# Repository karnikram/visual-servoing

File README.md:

<h1 align="center">Visual Servoing of Mobile Robot</h1>

This repo contains code for controlling a differential drive mobile robot within a map using images from an overhead camera. Uses thresholding and template matching for localization and a PID controller for generating the steering commands. The mobile robot uses an Arduino as its controller and LibSerial is used for communicating with it.

Also included are the PCB files for the mobile robot controller board.

<div align="center">

</div>

<a href="https://www.youtube.com/watch?v=kU-pIHazJII">Video</a>

### Libraries Used
* [OpenCV](https://github.com/opencv/opencv)
* [LibSerial](http://libserial.sourceforge.net/x27.html)

Based on [LOCK](https://github.com/QuinAsura/LOCK).

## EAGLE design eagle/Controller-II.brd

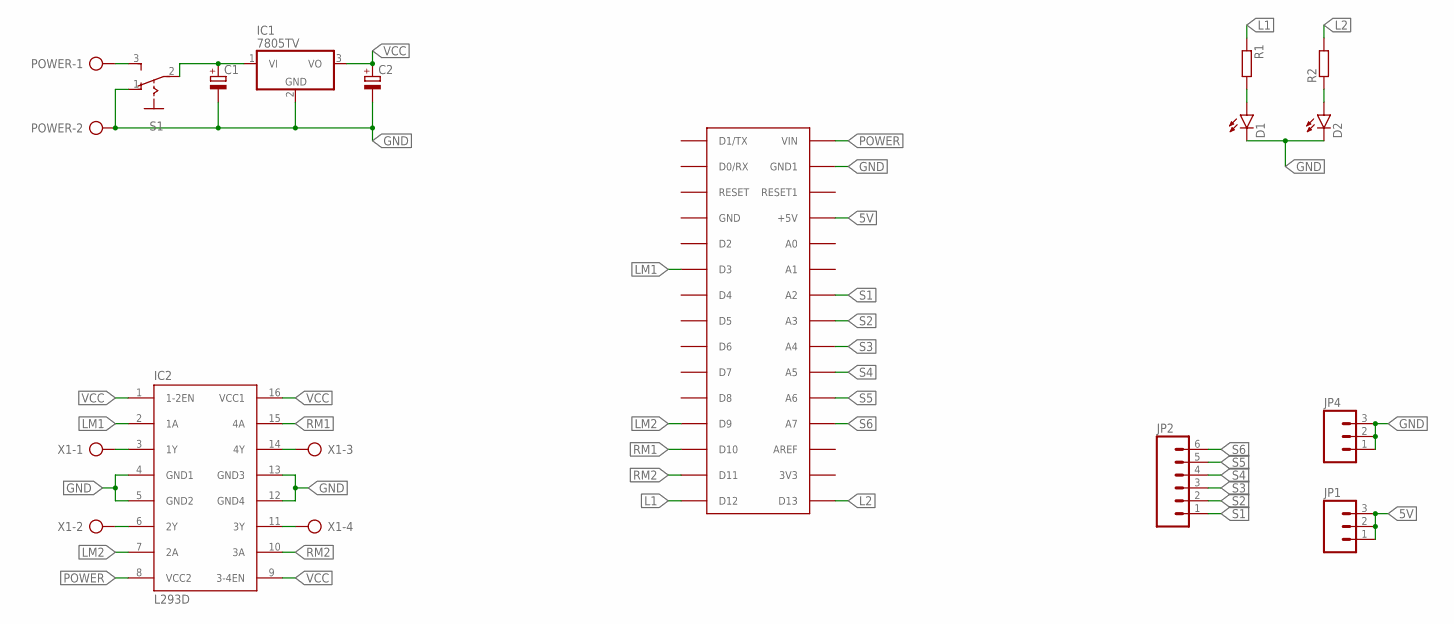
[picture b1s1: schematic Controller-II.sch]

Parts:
C1, C2: CPOL-EUE5-10.5; E5-10,5
D1, D2: LED5MM
IC1: 7805TV; TO220V
IC2: L293D; DIL16
JP1, JP4: M031X03_NO_SILK; 1X03_NO_SILK
JP2: M06NO_SILK_FEMALE_PTH; 1X06_NO_SILK
POWER: AK300/2
R1, R2: R-EU_0204/5; 0204/5
S1: 255SB
U1: ARDUINONANO; PDIP-32
X1: AK300/4

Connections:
5V: JP1.1, JP1.2, JP1.3, U1.+5V
7805: C1.+, IC1.1 (VI), S1.2
GND: C1.-, C2.-, D1.K (C), D2.K (C), IC1.2 (GND), IC2.4 (GND1), IC2.5 (GND2), IC2.12 (GND4), IC2.13 (GND3), JP4.1, JP4.2, JP4.3, POWER.2, S1.1 (O), U1.GND1
L1: R1.1, U1.D12
L2: R2.2, U1.D13
L02: IC2.6 (2Y), X1.2
LM1: IC2.2 (1A), U1.D3
LM2: IC2.7 (2A), U1.D9
LO1: IC2.3 (1Y), X1.1
unnamed: D1.A, R1.2
unnamed: D2.A, R2.1
POWER: IC2.8 (VCC2), POWER.1, S1.3 (S), U1.VIN
R01: IC2.14 (4Y), X1.3
R02: IC2.11 (3Y), X1.4
RM1: IC2.15 (4A), U1.D10
RM2: IC2.10 (3A), U1.D11
S1: JP2.1, U1.A2
S2: JP2.2, U1.A3
S3: JP2.3, U1.A4
S4: JP2.4, U1.A5
S5: JP2.5, U1.A6
S6: JP2.6, U1.A7
VCC: C2.+, IC1.3 (VO), IC2.1 (1-2EN), IC2.9 (3-4EN), IC2.16 (VCC1)

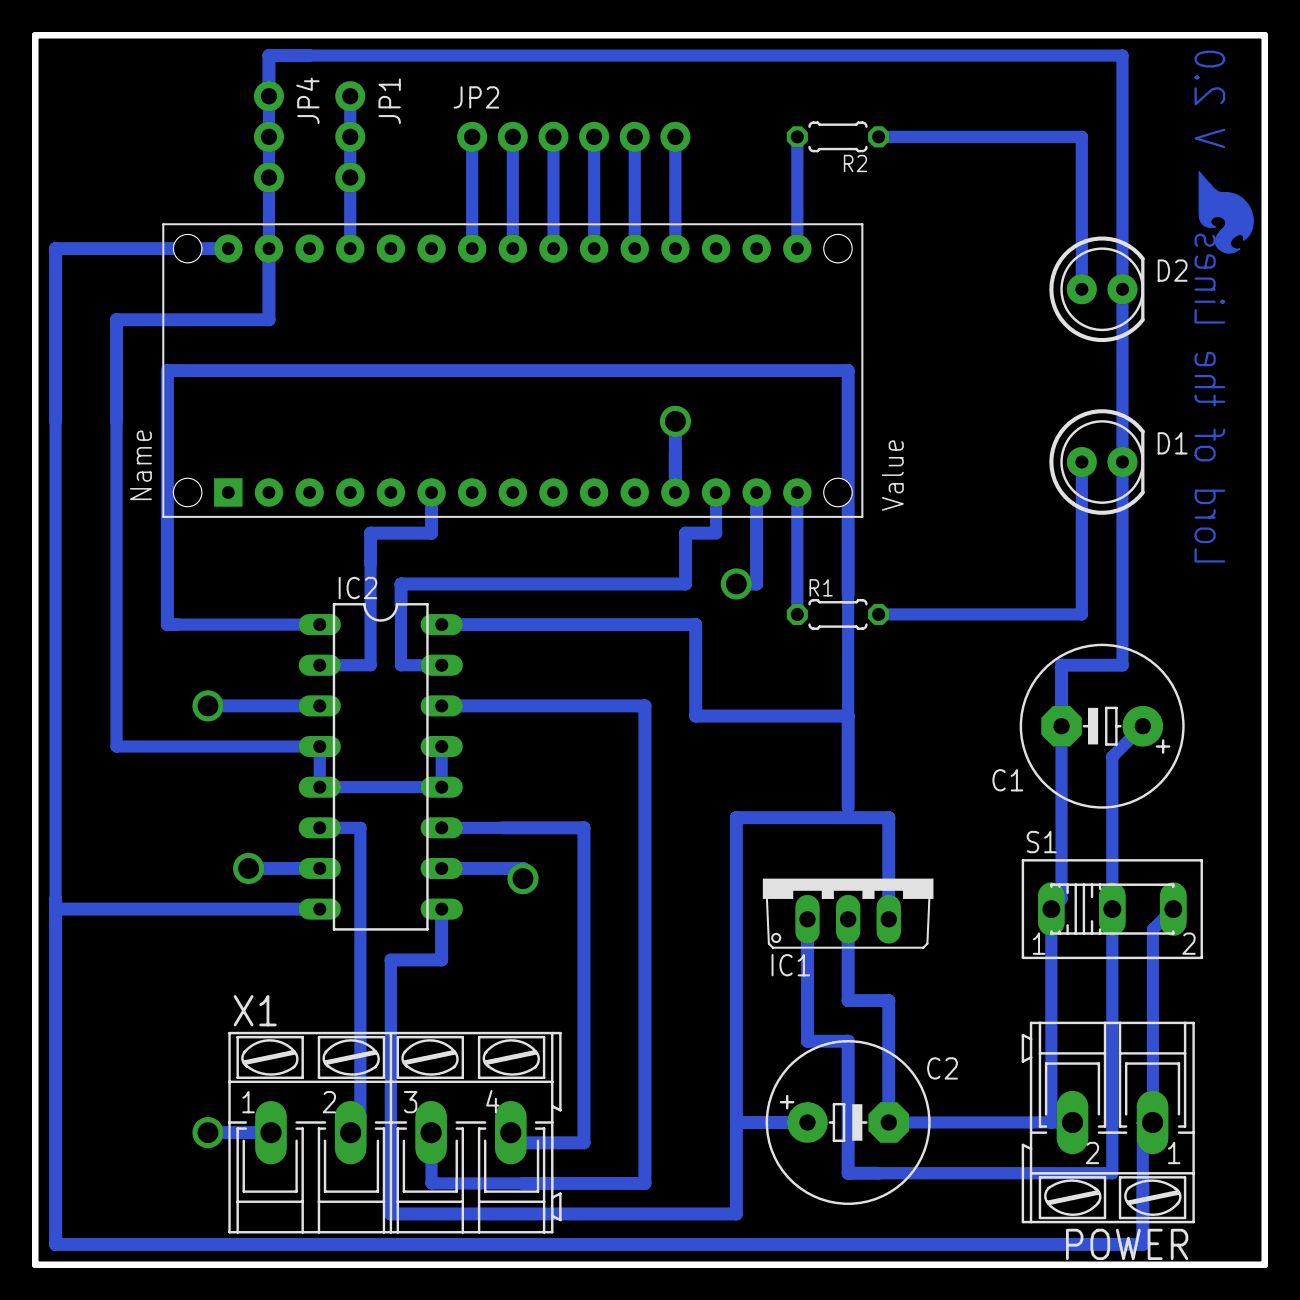
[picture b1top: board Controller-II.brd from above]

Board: 2 copper layers, 76.8 x 76.8 mm, 16 parts (1 on the bottom side), 23 nets.

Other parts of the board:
U$1: SFE_LOGO_FLAME_COPPER_.2

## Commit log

2018-09-27 Clean commit history

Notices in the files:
parts and their libraries:
SparkFun-LED: Licensing: Creative Commons ShareAlike 4.0 International - https://creativecommons.org/licenses/by-sa/4.0
